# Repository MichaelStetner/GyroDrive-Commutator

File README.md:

# GyroDrive-Commutator
GyroDrive-Commutator-Adaptor

## Pinout for X2
Oriented with X1 up and X2 down

|         |         |         |         |         |         |         |         |
|---------|---------|---------|---------|---------|---------|---------|---------|
|  CHAN2  |  CHAN3  |  ICOM   |   IX    |  AGND*  |  CHAN4  |  DGND^  |   SCL   |
|  CHAN1  | STIMOUT | STIMIN  |   V-    |   V+    |  AGND*  |  DGND^  |   SDA   |

\*Shorted to each other on board

^Shorted to each other on board

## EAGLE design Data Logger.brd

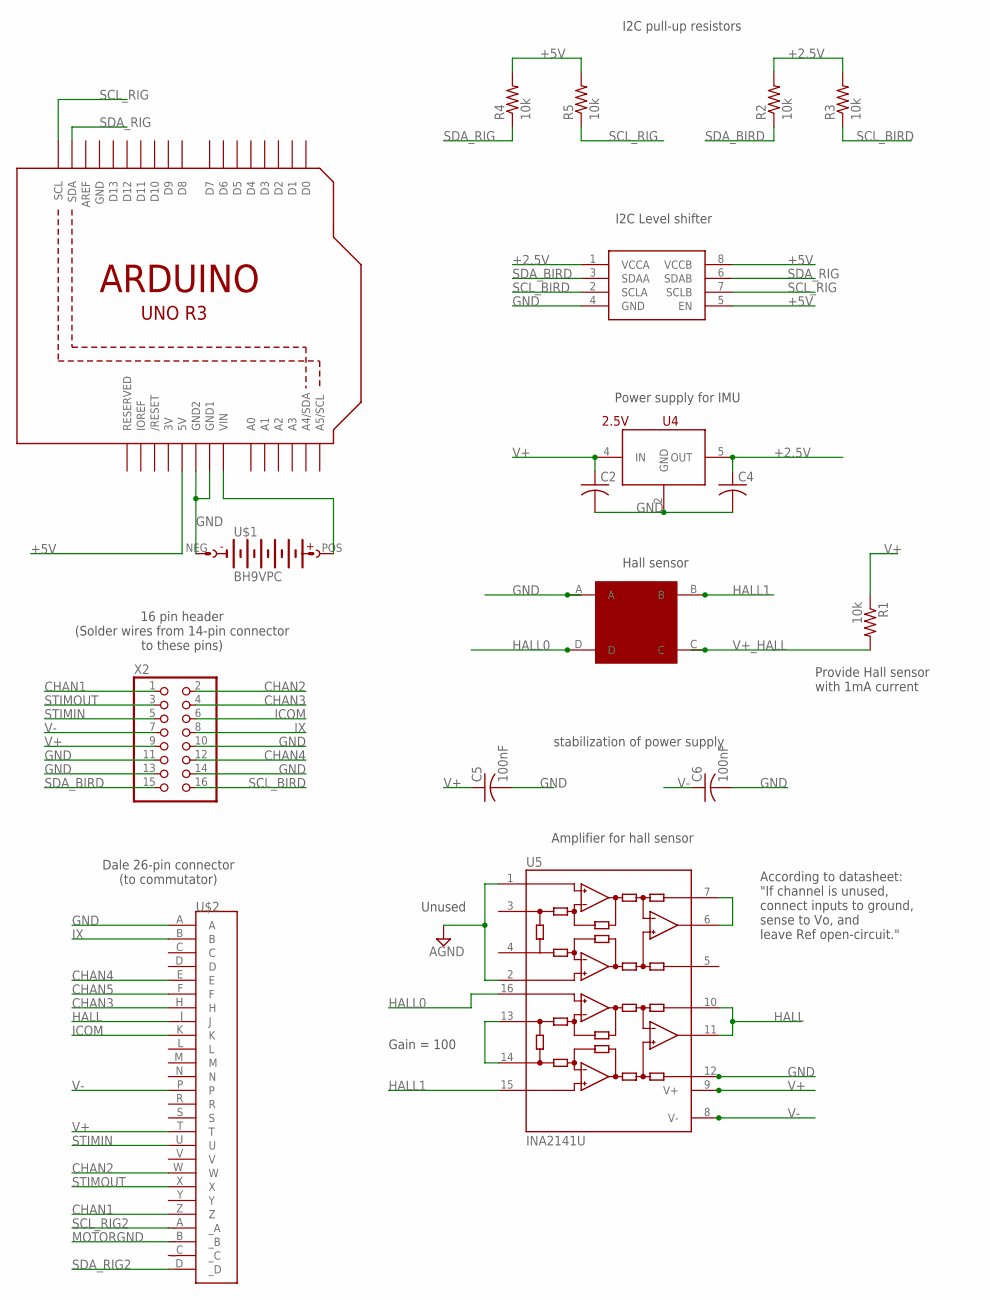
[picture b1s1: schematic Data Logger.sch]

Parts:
C2, C4: C-USC0402; C0402
C5, C6: 100nF; C0805
R1: 10k; R0805
R2, R3, R4, R5: 10k; R0402
U1: HALL; HALL_ON_SIDE
U2: PCA9517; SO-08
U4: 2.5V; SC70
U5: INA2141U; SO16-1
U6: ARDUINOR3-DIMENSION; ARDUINOR3
U$1: BH9VPC
U$2: MMD1P22G-26-M101
X2: PINHD-2X8; 2X08

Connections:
3V: U6.3V
+2.5V: C4.1, R2.2, R3.2, U2.1 (VCCA), U4.5 (OUT)
+5V: R4.2, R5.2, U2.5 (EN), U2.8 (VCCB), U6.5V
+9V: U6.VIN, U$1.POS
CHAN1: U$2.Z, X2.1
CHAN2: U$2.W, X2.2
CHAN3: U$2.H, X2.4
CHAN4: U$2.E, X2.12
CHAN5: U$2.F
GND: C2.2, C4.2, C5.2, C6.2, U1.A, U2.4 (GND), U4.2 (GND), U5.1 (INA-), U5.2 (INA+), U5.12 (REFB), U6.GND, U6.GND1, U6.GND2, U$1.NEG, U$2.A, X2.10, X2.11, X2.13, X2.14
HALL: U5.10 (SENSEB), U5.11 (VOB), U$2.J
HALL0: U1.D, U5.16 (INB-)
HALL1: U1.B, U5.15 (INB+)
ICOM: U$2.K, X2.6
IX: U$2.B, X2.8
MOTORGND: U$2._B
unnamed: U5.13 (JB), U5.14 (JB)
SCL_BIRD: R3.1, U2.2 (SCLA), X2.16
SCL_RIG: R5.1, U2.7 (SCLB), U6.SCL
SCL_RIG2: U$2._A
SDA_BIRD: R2.1, U2.3 (SDAA), X2.15
SDA_RIG: R4.1, U2.6 (SDAB), U6.SDA
SDA_RIG2: U$2._D
STIMIN: U$2.U, X2.5
STIMOUT: U$2.X, X2.3
UNUSED: U5.6 (VOA), U5.7 (SENSEA)
V+: C2.1, C5.1, R1.1, U4.4 (IN), U5.9 (V+), U$2.T, X2.9
V+_HALL: R1.2, U1.C
V-: C6.1, U5.8 (V-), U$2.P, X2.7

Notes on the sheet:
stabilization of power supply
Hall sensor
Amplifier for hall sensor
Gain = 100
Unused
Provide Hall sensor with 1mA current
16 pin header (Solder wires from 14-pin connector to these pins)
According to datasheet: "If channel is unused, connect inputs to ground, sense to Vo, and leave Ref open-circuit."
I2C pull-up resistors
Dale 26-pin connector (to commutator)
I2C Level shifter
Power supply for IMU

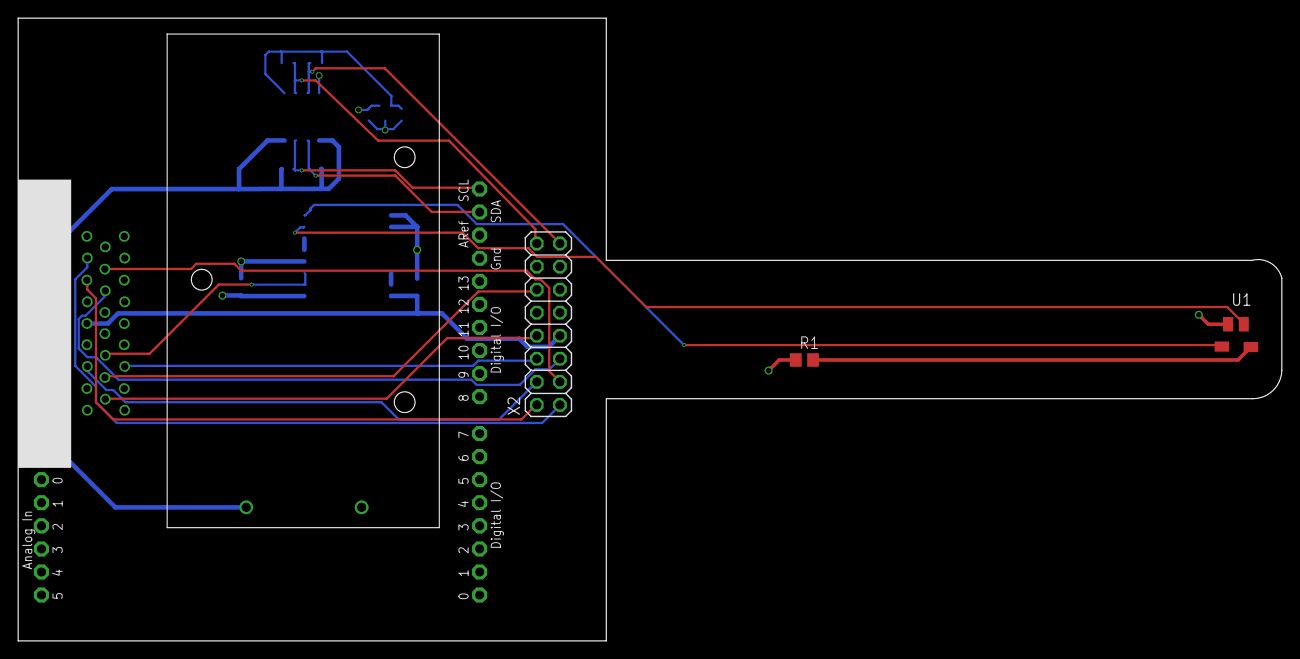
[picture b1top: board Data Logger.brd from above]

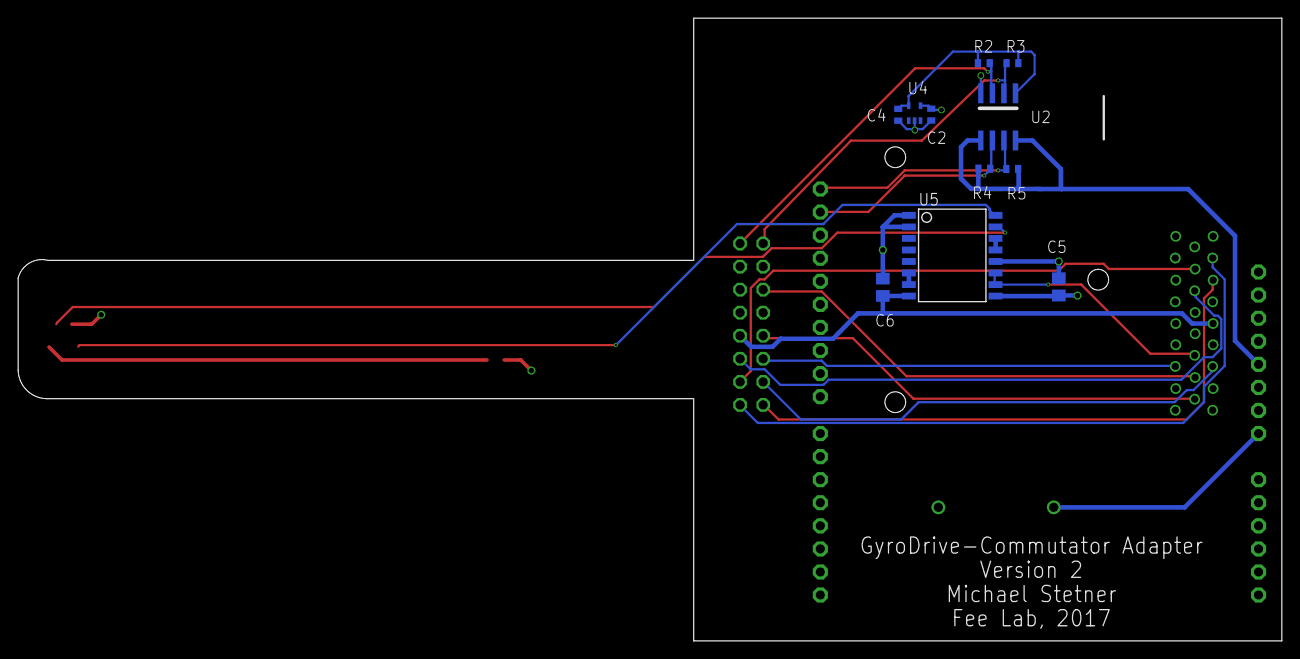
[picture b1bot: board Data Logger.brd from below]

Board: 4 copper layers, 139.2 x 68.6 mm, 17 parts (11 on the bottom side), 24 nets.

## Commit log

2016-02-03 Added 5ch pre-amp from Tatuso. This will be the basis of my designs.
2016-02-03 Removed VGROUND and changed JMP1 pinout
2016-02-03 Made board into 4 layers. Put in resistors for voltage dividers
2016-02-04 Finished routing
2016-02-05 added parts list
2016-02-05 Shortened board by 0.75 inches to make room for DB25-Dale adapter
2016-02-06 I2C pull-up resistors added
2016-02-06 Fixed stop mask DRC errors on some resistors and capacitors
2016-02-08 no message
2016-02-08 Removed instrumentation amplifiers for electrodes
2016-02-08 Added more bypass capacitors (one for each power supply on each instrumentation amp)
2016-02-08 Fixed silk screen
2016-02-09 narrower board - removed empty space
2016-02-09 Updated parts list - more bypass capacitors and higher voltage rating
2016-02-09 Updated parts list - added I2C pull up resistors (R10-R11)
2016-03-18 Added orientation marker for PCA9517 to silkscreen
2016-04-11 Updated README with pinout for X2
2017-02-09 redesign as an arduino shield
2017-02-24 Add orientation marker for U2
2019-01-01 schematic and layout formatting for thesis
